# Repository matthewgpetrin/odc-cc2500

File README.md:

Copyright © 2026 Matthew Petrin

Liscenses are annoying. Please feel free to use this design for any personal projects. Please do not sell any products using this design without my express permission. And of course, follow any local RF regulations.

---
<kbd> 
	 
</kbd>

---
<kbd> 
	 
</kbd>

## About:
This repo contains KiCAD files and fabrication outputs for a simple breakout board designed around the CC2500 transceiver. The board features a 0.1" pitch header providing access to the IC's control pins, and an SMA header on the RF output.

The board is to be powered by a 5V DC source, which is regulated down to 3.3V. Power can be provided via the rectangular header, or via USB C.

The project is designed in KiCAD 9, and should be compatible with equal or greater versions. All required symbols and footprints are contained within.

## Part Selection:
A BOM is provided in the repo. There are a few components which may be affected by manufacturing processes:

The choice of termination capacitors around the crystal resonator will depend on board parasitics - see the CC2500 datasheet for further details

The choice of current-limiting resistor on the power LED will obviously depend on the forward voltage of the selected LED and the desired brightness.

The series termination resistors on the CC2500 may need to be adjusted/shorted depending on bus impedance, bus length, edge rate, and external capacitance.

## Directories:
`assets`: Images associated with documentation.

`docs`: Currently empty. May be updated in the future.

`fab`: Files required for board fabrication and assembly (bill-of-materials, gerbers, schematics, and position files).

`kicad`: KiCAD project files, including schematic, layout, symbols, footprints, and design rules.

## Other Notes:
Board mounting holes are compatible with m3 or 4-40 screws, and are spaced 26x18 mm.

As of rev. 1.0, the mounting holes are not grounded.

## Datasheets:
[CC2500](https://www.ti.com/lit/ds/symlink/cc2500.pdf?ts=1783648273403&)

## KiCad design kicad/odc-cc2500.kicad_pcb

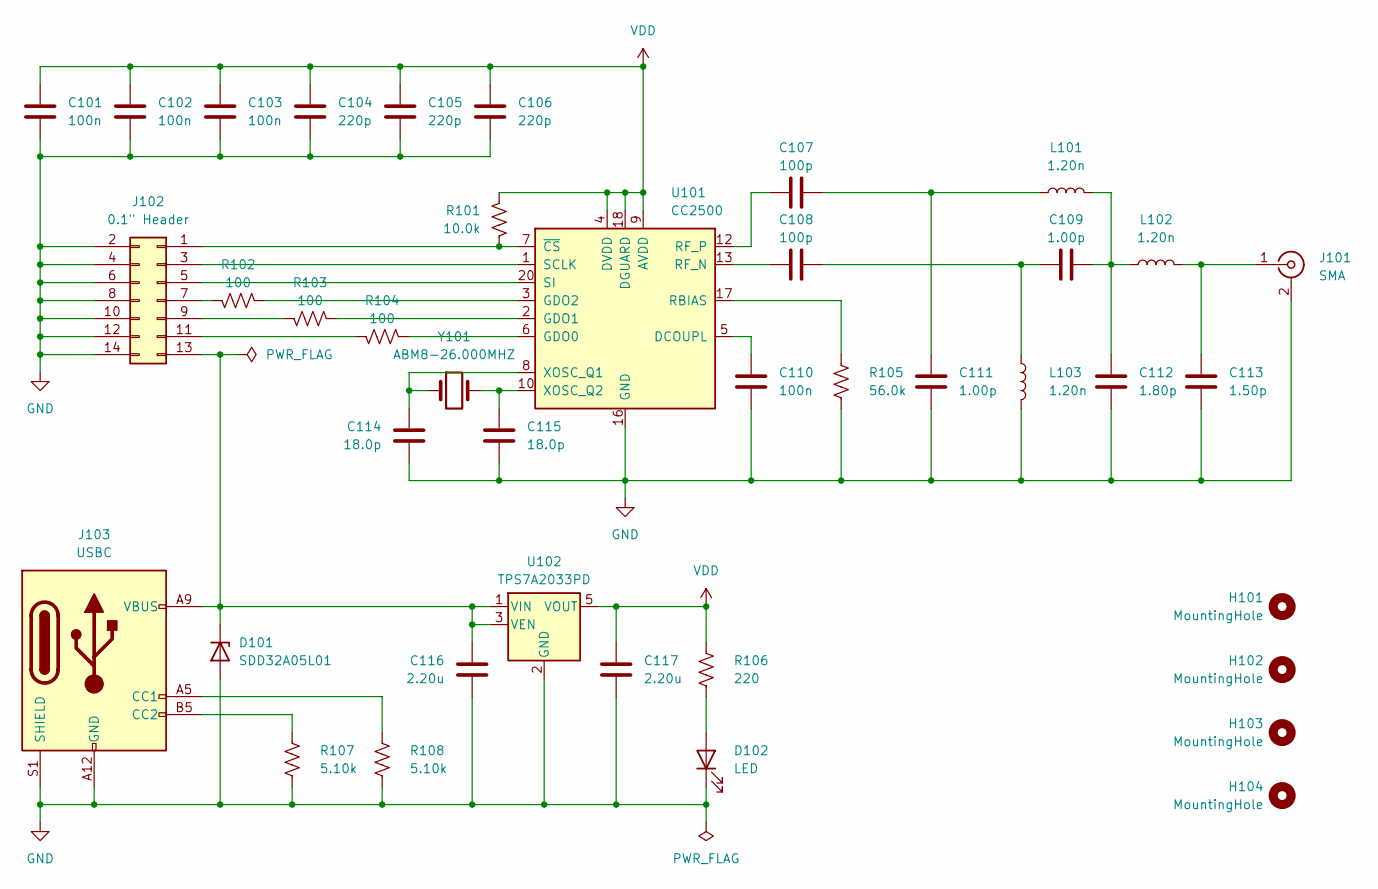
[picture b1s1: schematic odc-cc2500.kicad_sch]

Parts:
C101, C102, C103, C110: 100n; C_0402_1005Metric; Mfr. PN GCM155R71H104KE02D; Digikey PN 490-10672-1-ND
C104, C105, C106: 220p; C_0402_1005Metric; Mfr. PN GRM1555C1H221JA01D; Digikey PN 490-1293-1-ND
C107, C108: 100p; C_0402_1005Metric; Mfr. PN GRM1555C1H101JA01D; Digikey PN 490-5922-1-ND
C109, C111: 1.00p; C_0402_1005Metric; Mfr. PN GRM1555C1H1R0BA01D; Digikey PN 490-6206-1-ND
C112: 1.80p; C_0402_1005Metric; Mfr. PN GJM1555C1H1R8BB01D; Digikey PN 490-8089-1-ND
C113: 1.50p; C_0402_1005Metric; Mfr. PN GJM1555C1H1R5BB01D; Digikey PN 490-8087-1-ND
C114, C115: 18.0p; C_0402_1005Metric; Mfr. PN GRM1555C1H180JA01D; Digikey PN 490-5858-1-ND
C116, C117: 2.20u; C_0402_1005Metric; Mfr. PN GRM155Z71A225KE44D; Digikey PN 490-GRM155Z71A225KE44DCT-ND
D101: SDD32A05L01; D_SOD-323; Mfr. PN SDD32A05L01; Digikey PN 13-SDD32A05L01CT-ND
D102: LED; LED_0603_1608Metric; Mfr. PN SML-D12M8WT86; Digikey PN 846-SML-D12M8WT86CT-ND
H101, H102, H103, H104: MountingHole; MountingHole_3.2mm_M3_DIN965_Pad
J101: SMA; SMA_Samtec_SMA-J-P-H-ST-EM1_EdgeMount; Mfr. PN SMA-J-P-H-ST-EM1; Digikey PN SAM8857-ND
J102: 0.1" Header; PinHeader_2x07_P2.54mm_Vertical; Mfr. PN PH2-14-UA; Digikey PN 2057-PH2-14-UA-ND
J103: USBC; USB_C_Receptacle_HRO_TYPE-C-31-M-17; Mfr. PN 10164359-00011LF; Digikey PN 609-10164359-00011LFCT-ND
L101, L102, L103: 1.20n; L_0402_1005Metric; Mfr. PN LQG15HS1N2B02D; Digikey PN 490-LQG15HS1N2B02DCT-ND
R101: 10.0k; R_0402_1005Metric; Mfr. PN ERJ-2GEJ103X; Digikey PN P10KJCT-ND
R102, R103, R104: 100; R_0402_1005Metric; Mfr. PN ERJ-2GEJ101X; Digikey PN P100JCT-ND
R105: 56.0k; R_0402_1005Metric; Mfr. PN ERJ-2RKF5602X; Digikey PN P56.0KLCT-ND
R106: 220; R_0402_1005Metric; Mfr. PN ERJ-2RKF2200X; Digikey PN P220LCT-ND
R107, R108: 5.10k; R_0402_1005Metric; Mfr. PN ERJ-2RKF5101X; Digikey PN P5.10KLCT-ND
U101: CC2500; Texas_RGP0020H_VQFN-20-1EP_4x4mm_P0.5mm_EP2.4x2.4mm; Mfr. PN CC2500RGPR; Digikey PN 296-38562-1-ND
U102: TPS7A2033PD; SOT-23-5; Mfr. PN TPS7A2033PDBVR; Digikey PN 296-TPS7A2033PDBVRCT-ND
Y101: ABM8-26.000MHZ; Crystal_SMD_3225-4Pin_3.2x2.5mm; Mfr. PN ABM8-26.000MHz-10-D-1-G-T; Digikey PN 535-15004-1-ND

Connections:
GND: C101.1, C102.1, C103.1, C104.1, C105.1, C106.1, C110.1, C111.1, C112.1, C113.1, C114.1, C115.1, C116.1, C117.1, D101.2 (A), D102.1 (K), J101.2 (Ext), J102.2, J102.4, J102.6, J102.8, J102.10, J102.12, J102.14, J103.A12 (GND), J103.B12 (GND), J103.S1 (SHIELD), L103.1, R105.2, R107.2, R108.2, U101.16 (GND), U101.19 (GND), U101.21 (GND), U102.2 (GND)
unnamed: C107.1, C111.2, L101.2
unnamed: C108.1, C109.2, L103.2
unnamed: C109.1, C112.2, L101.1, L102.2
unnamed: C116.2, D101.1 (K), J102.13, J103.A9 (VBUS), J103.B9 (VBUS), U102.1 (VIN), U102.3 (VEN)
unnamed: D102.2 (A), R106.2
unnamed: C113.2, J101.1 (In), L102.1
unnamed: J102.1, R101.2, U101.7 (~CS)
unnamed: J102.3, U101.1 (SCLK)
unnamed: J102.5, U101.20 (SI)
unnamed: J102.7, R102.2
unnamed: J102.9, R103.2
unnamed: J102.11, R104.2
unnamed: J103.A5 (CC1), R108.1
unnamed: J103.B5 (CC2), R107.1
unnamed: C110.2, U101.5 (DCOUPL)
unnamed: R104.1, U101.6 (GDO0)
unnamed: R103.1, U101.2 (GDO1)
unnamed: R102.1, U101.3 (GDO2)
unnamed: R105.1, U101.17 (RBIAS)
unnamed: C108.2, U101.13 (RF_N)
unnamed: C107.2, U101.12 (RF_P)
unnamed: C114.2, U101.8 (XOSC_Q1), Y101.1
unnamed: C115.2, U101.10 (XOSC_Q2), Y101.3
VDD: C101.2, C102.2, C103.2, C104.2, C105.2, C106.2, C117.2, R101.1, R106.1, U101.4 (DVDD), U101.9 (AVDD), U101.11 (AVDD), U101.14 (AVDD), U101.15 (AVDD), U101.18 (DGUARD), U102.5 (VOUT)

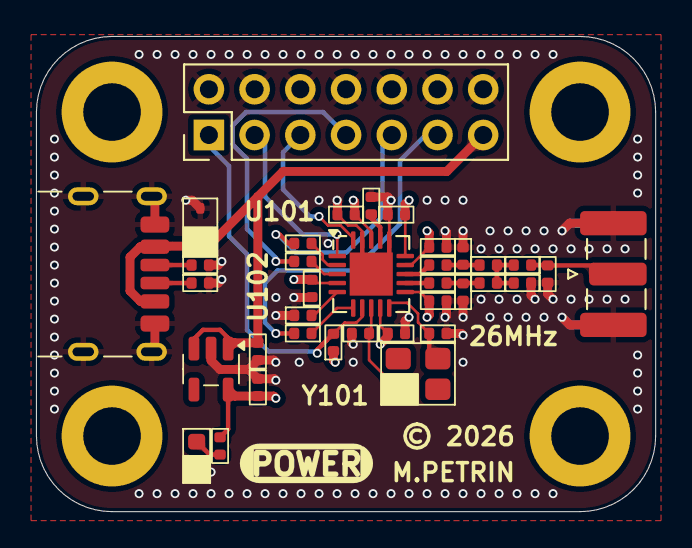
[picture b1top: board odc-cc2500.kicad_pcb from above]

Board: 4 copper layers, 34.4 x 26.4 mm, 40 parts (0 on the bottom side), 25 nets.

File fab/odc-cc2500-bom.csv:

"Reference","Qty","Value","Manufacturer","Mfr. PN","Digikey PN","Mouser PN"
"C101,C102,C103,C110","4","100n","Murata","GCM155R71H104KE02D","490-10672-1-ND","81-GCM155R71H104KE2D"
"C104,C105,C106","3","220p","Murata","GRM1555C1H221JA01D","490-1293-1-ND","81-GRM1555C1H221JA01"
"C107,C108","2","100p","Murata","GRM1555C1H101JA01D","490-5922-1-ND","81-GRM1555C1H101JA1D"
"C109,C111","2","1.00p","Murata","GRM1555C1H1R0BA01D","490-6206-1-ND","81-GRM1555C1H1R0BA1D"
"C112","1","1.80p","Murata","GJM1555C1H1R8BB01D","490-8089-1-ND","81-GJM1555C1H1R8BB01"
"C113","1","1.50p","Murata","GJM1555C1H1R5BB01D","490-8087-1-ND","81-GJM1555C1H1R5BB1D"
"C114,C115","2","18.0p","Murata","GRM1555C1H180JA01D","490-5858-1-ND","81-GRM1555C1H180JA1D"
"C116,C117","2","2.20u","Murata","GRM155Z71A225KE44D","490-GRM155Z71A225KE44DCT-ND","81-GRM155Z71A225KE4D"
"D101","1","SDD32A05L01","YAGEO","SDD32A05L01","13-SDD32A05L01CT-ND","603-SDD32A05L01"
"D102","1","LED","Rohm","SML-D12M8WT86","846-SML-D12M8WT86CT-ND","755-SML-D12M8WT86"
"J101","1","SMA","Samtec","SMA-J-P-H-ST-EM1","SAM8857-ND","200-SMAJPHSTEM1"
"J102","1","0.1"" Header","Adam Tech","PH2-14-UA","2057-PH2-14-UA-ND","737-PH2-14-UA"
"J103","1","USBC","Amphenol ICC","10164359-00011LF","609-10164359-00011LFCT-ND","649-10164359-00011LF"
"L101,L102,L103","3","1.20n","Murata","LQG15HS1N2B02D","490-LQG15HS1N2B02DCT-ND","81-LQG15HS1N2B02D"
"R101","1","10.0k","Panasonic","ERJ-2GEJ103X","P10KJCT-ND","667-ERJ-2GEJ103X"
"R102,R103,R104","3","100","Panasonic","ERJ-2GEJ101X","P100JCT-ND","667-ERJ-2GEJ101X"
"R105","1","56.0k","Panasonic","ERJ-2RKF5602X","P56.0KLCT-ND","667-ERJ-2RKF5602X"
"R106","1","220","Panasonic","ERJ-2RKF2200X","P220LCT-ND","667-ERJ-2RKF2200X"
"R107,R108","2","5.10k","Panasonic","ERJ-2RKF5101X","P5.10KLCT-ND","667-ERJ-2RKF5101X"
"U101","1","CC2500","Texas Instruments","CC2500RGPR","296-38562-1-ND","595-CC2500RGPR"
"U102","1","TPS7A2033PD","Texas Instruments","TPS7A2033PDBVR","296-TPS7A2033PDBVRCT-ND","595-TPS7A2033PDBVR"
"Y101","1","ABM8-26.000MHZ","Abracon","ABM8-26.000MHz-10-D-1-G-T","535-15004-1-ND","815-M826000MHZ10D1GT"
